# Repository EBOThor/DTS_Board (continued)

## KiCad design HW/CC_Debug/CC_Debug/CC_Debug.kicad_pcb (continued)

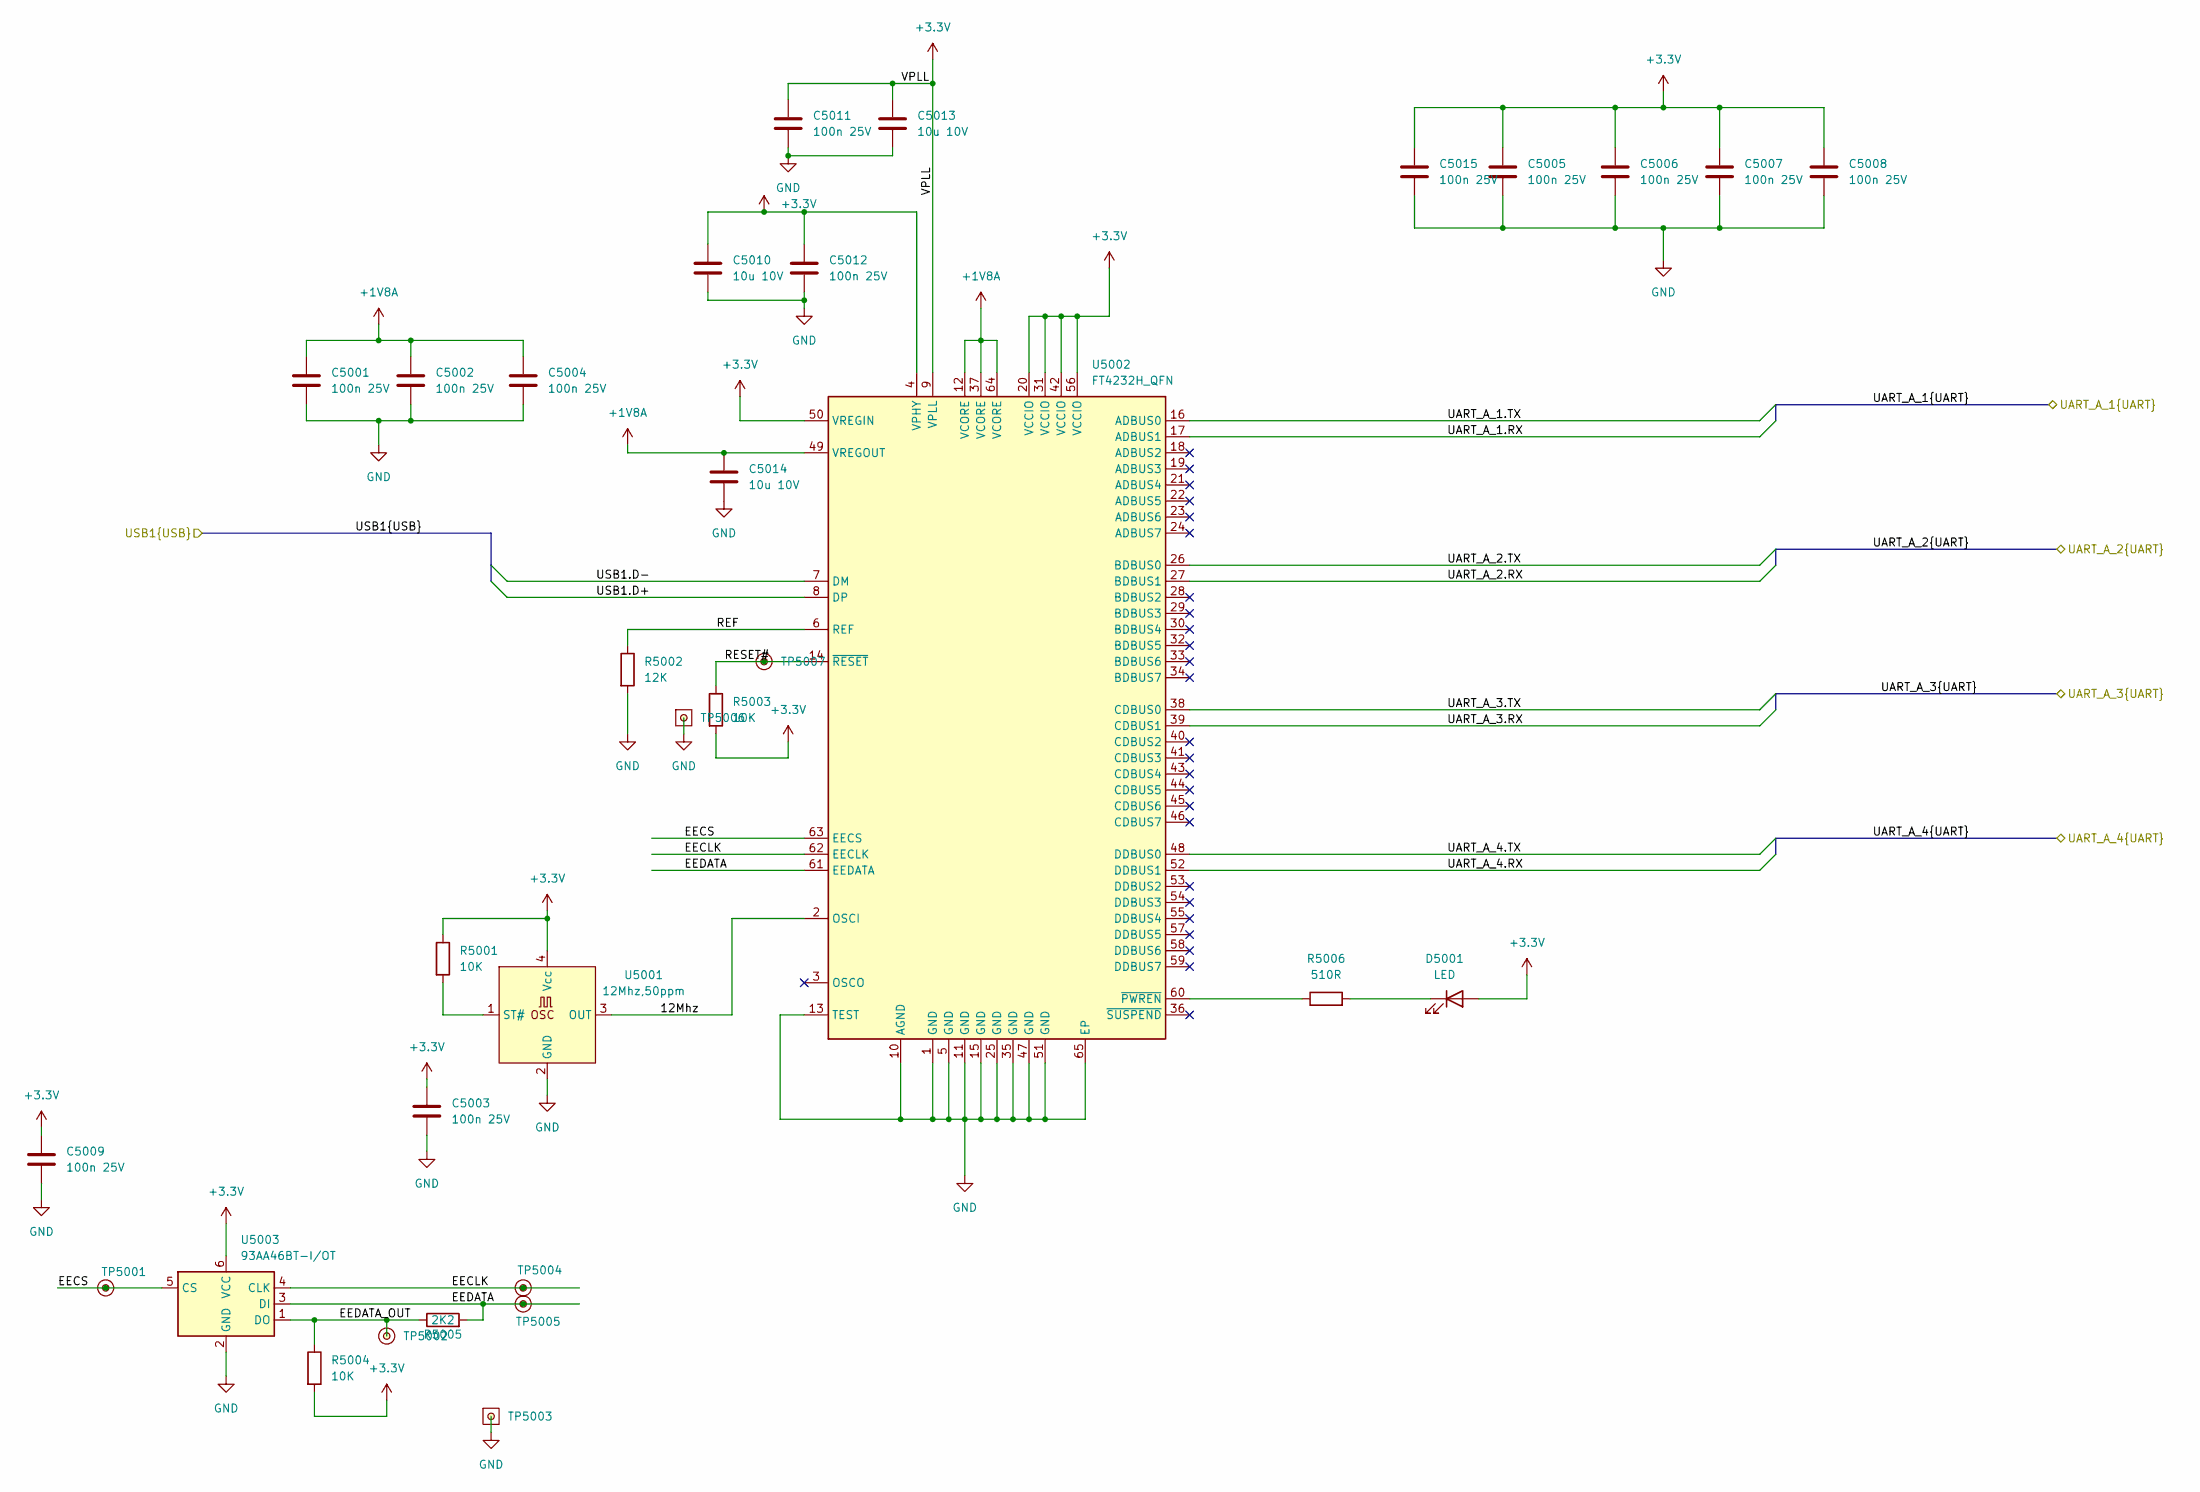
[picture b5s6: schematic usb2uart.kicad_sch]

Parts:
C5001, C5002, C5003, C5004, C5005, C5006, C5007, C5008, C5009, C5011, C5012, C5015: 100n 25V; C_0603_1608Metric; MPN C;C;T1;S;P0603;NA
C5010, C5013, C5014: 10u 10V; C_0603_1608Metric; MPN C;C;T1;S;P0603;NA
D5001: LED; LED_0603_1608Metric
R5001, R5003, R5004: 10K; R_0603_1608Metric; MPN R;G;T1;S;P0603;NA
R5002: 12K; R_0603_1608Metric; MPN R;G;T1;S;P0603;NA
R5005: 2K2; R_0603_1608Metric; MPN R;G;T1;S;P0603;NA
R5006: 510R; R_0603_1608Metric; MPN R;G;T1;S;P0603;NA
TP5001, TP5002, TP5004, TP5005, TP5007: TestPoint; TestPoint_THTPad_D1.0mm_Drill0.5mm
TP5003, TP5006: TestPoint; TestPoint_THTPad_1.0x1.0mm_Drill0.5mm
U5001: 12Mhz,50ppm; Oscillator_SMD_SeikoEpson_SG8002CE-4Pin_3.2x2.5mm; MPN SG3225CAN 12.0000M-TJGA6
U5002: FT4232H_QFN; QFN-64-1EP_9x9mm_P0.5mm_EP4.35x4.35mm; MPN FT4232HP
U5003: 93AA46BT-I/OT; SOT-23-6; MPN 93AA46BT-I/OT

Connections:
+1V8A: C5001.1, C5002.1, C5004.1, C5014.1, U5002.12 (VCORE), U5002.37 (VCORE), U5002.49 (VREGOUT), U5002.64 (VCORE)
+3.3V: C5003.1, C5005.1, C5006.1, C5007.1, C5008.1, C5009.1, C5010.1, C5011.1, C5012.1, C5013.1, C5015.1, D5001.2 (A), R5001.1, R5003.2, R5004.2, U5001.4 (Vcc), U5002.4 (VPHY), U5002.9 (VPLL), U5002.20 (VCCIO), U5002.31 (VCCIO), U5002.42 (VCCIO), U5002.50 (VREGIN), U5002.56 (VCCIO), U5003.6 (VCC); also elsewhere on the board
/Isolation_output/UART_A_1.RX: U5002.17 (ADBUS1); also elsewhere on the board
/Isolation_output/UART_A_1.TX: U5002.16 (ADBUS0); also elsewhere on the board
/Isolation_output/UART_A_2.RX: U5002.27 (BDBUS1); also elsewhere on the board
/Isolation_output/UART_A_2.TX: U5002.26 (BDBUS0); also elsewhere on the board
/Isolation_output/UART_A_3.RX: U5002.39 (CDBUS1); also elsewhere on the board
/Isolation_output/UART_A_3.TX: U5002.38 (CDBUS0); also elsewhere on the board
/Isolation_output/UART_A_4.RX: U5002.52 (DDBUS1); also elsewhere on the board
/Isolation_output/UART_A_4.TX: U5002.48 (DDBUS0); also elsewhere on the board
/USB1.D+: U5002.8 (DP); also elsewhere on the board
/USB1.D-: U5002.7 (DM); also elsewhere on the board
/USB2UART1/12Mhz: U5001.3 (OUT), U5002.2 (OSCI)
/USB2UART1/EECLK: TP5004.1, U5002.62 (EECLK), U5003.4 (CLK)
/USB2UART1/EECS: TP5001.1, U5002.63 (EECS), U5003.5 (CS)
/USB2UART1/EEDATA: R5005.2, TP5005.1, U5002.61 (EEDATA), U5003.3 (DI)
/USB2UART1/EEDATA_OUT: R5004.1, R5005.1, TP5002.1, U5003.1 (DO)
/USB2UART1/REF: R5002.1, U5002.6 (REF)
/USB2UART1/RESET#: R5003.1, TP5007.1, U5002.14 (~RESET)
GND: C5001.2, C5002.2, C5003.2, C5004.2, C5005.2, C5006.2, C5007.2, C5008.2, C5009.2, C5010.2, C5011.2, C5012.2, C5013.2, C5014.2, C5015.2, R5002.2, TP5003.1, TP5006.1, U5001.2 (GND), U5002.1 (GND), U5002.5 (GND), U5002.10 (AGND), U5002.11 (GND), U5002.13 (TEST), U5002.15 (GND), U5002.25 (GND), U5002.35 (GND), U5002.47 (GND), U5002.51 (GND), U5002.65 (EP), U5003.2 (GND); also elsewhere on the board
unnamed: D5001.1 (K), R5006.2
unnamed: R5001.2, U5001.1 (ST#)
unnamed: R5006.1, U5002.60 (~PWREN)

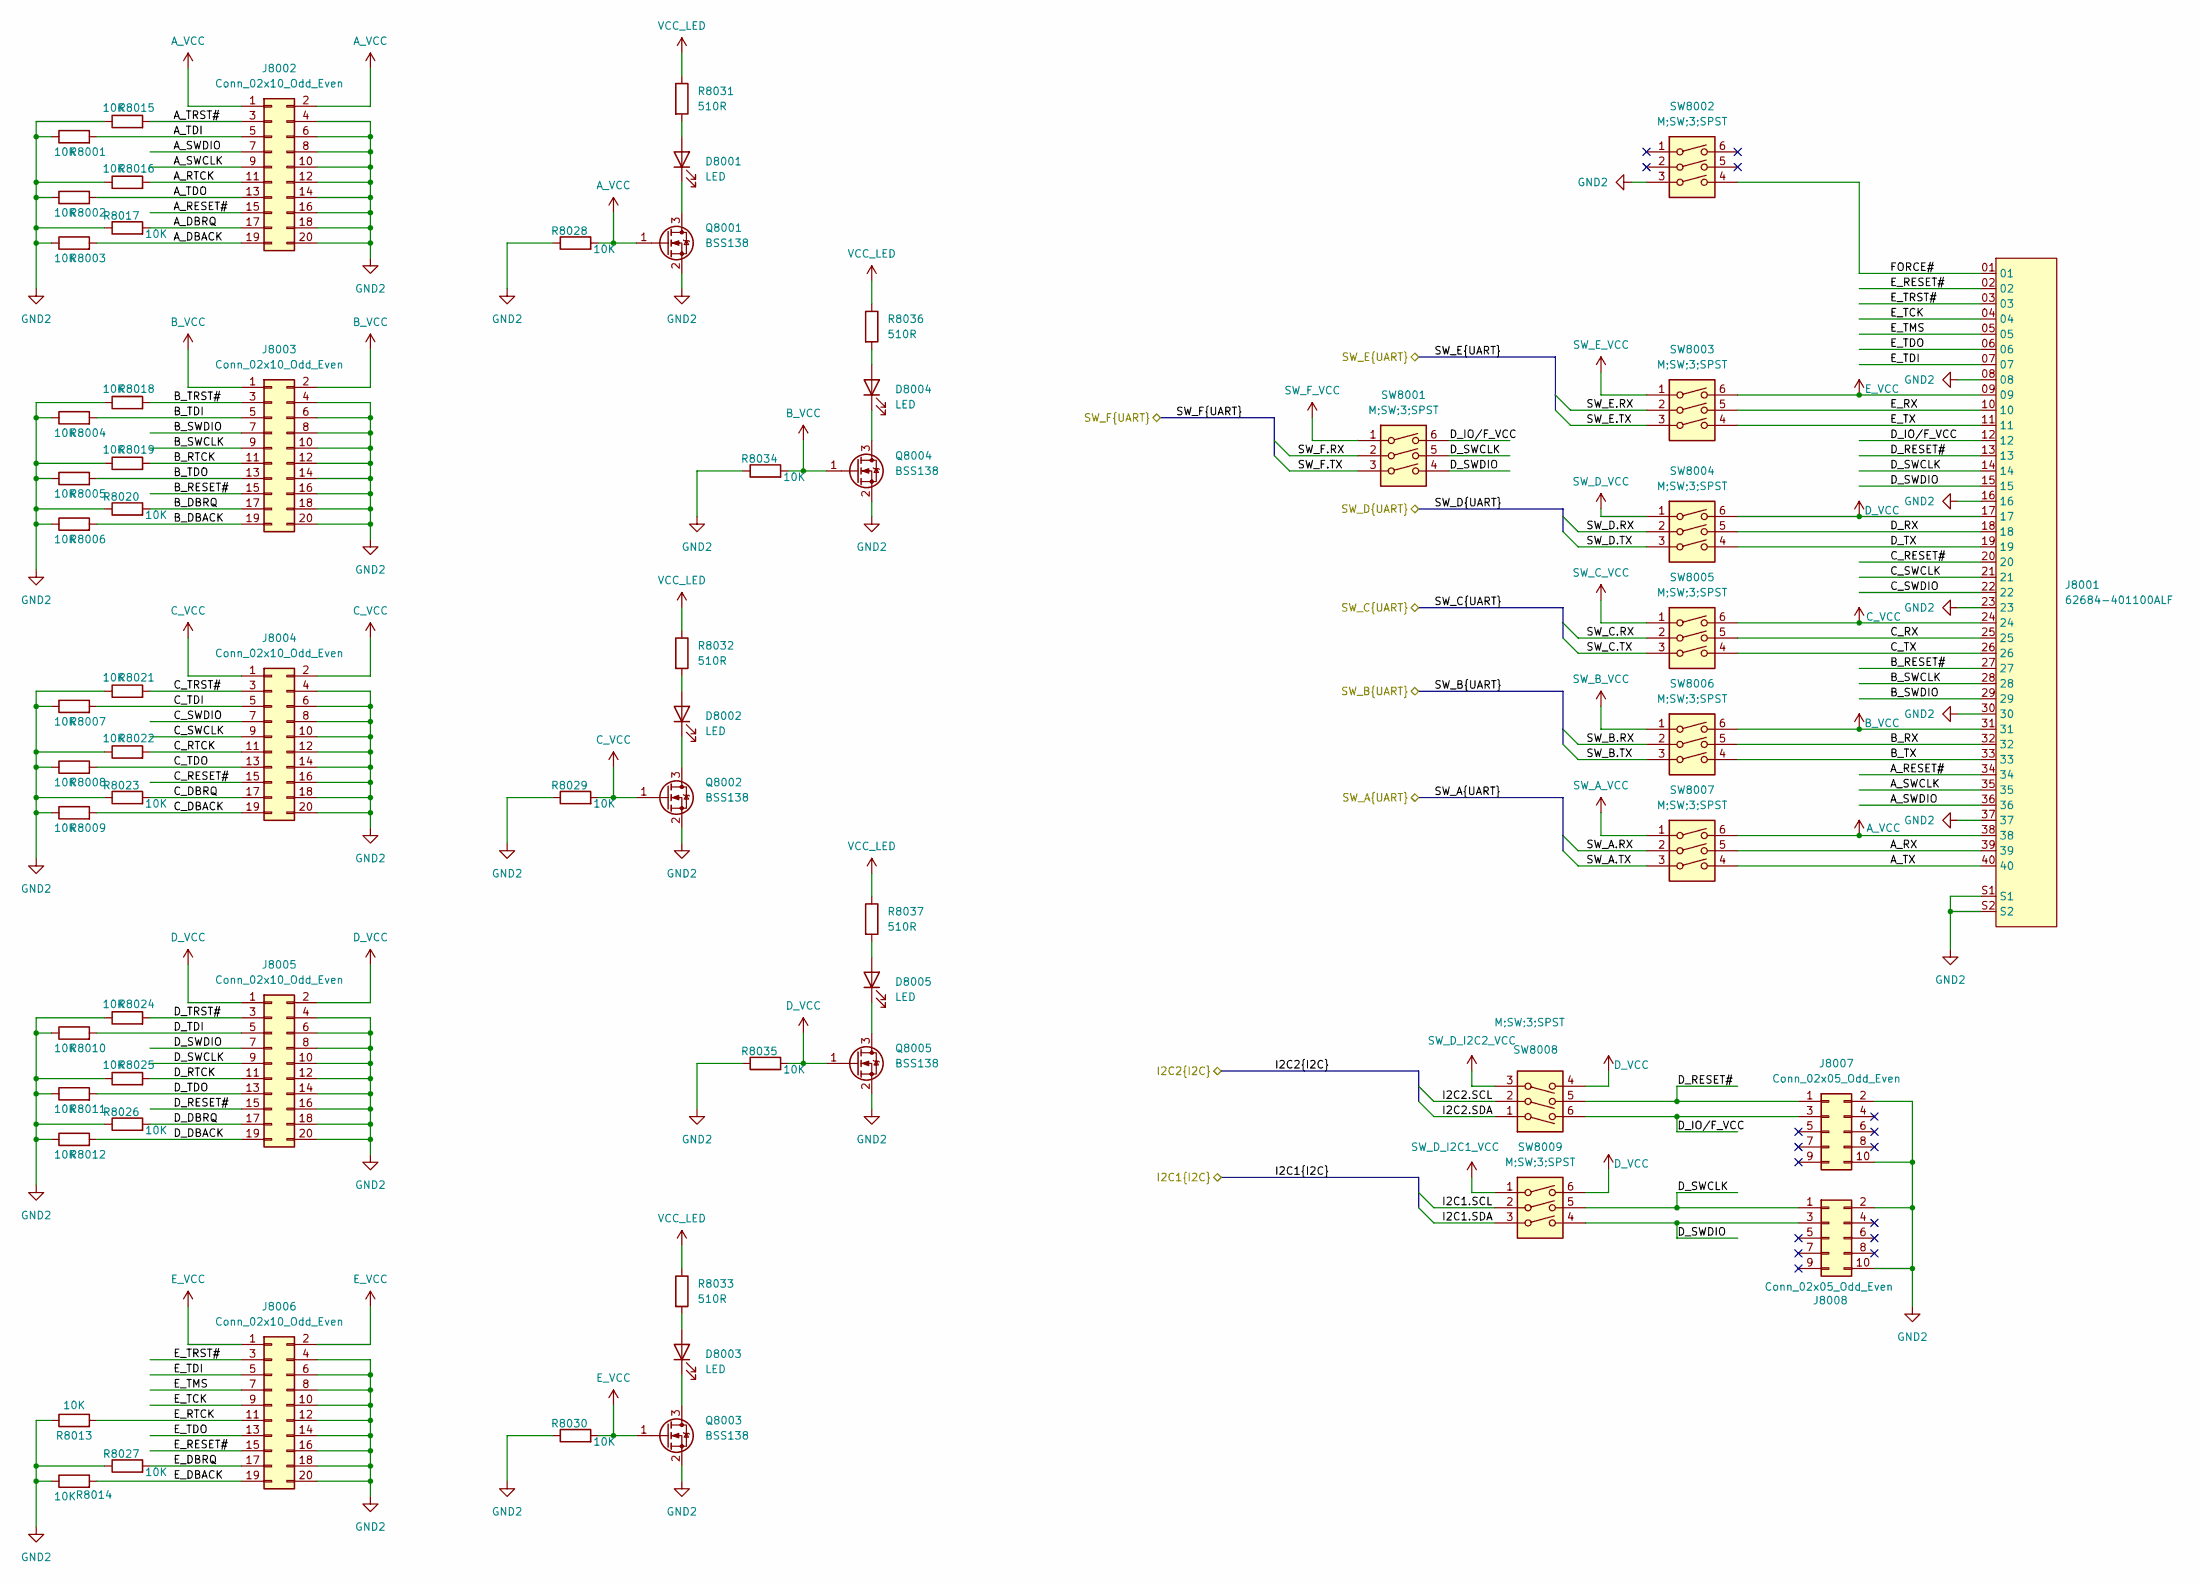
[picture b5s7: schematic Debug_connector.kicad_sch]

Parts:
D8001, D8002, D8003, D8004, D8005: LED; LED_0603_1608Metric
J8001: 62684-401100ALF; MPN 62684-401100ALF
J8002, J8003, J8004, J8005, J8006: Conn_02x10_Odd_Even; IDC-Header_2x10_P2.54mm_Vertical
J8007, J8008: Conn_02x05_Odd_Even; IDC-Header_2x05_P2.54mm_Vertical
Q8001, Q8002, Q8003, Q8004, Q8005: BSS138; SOT-23
R8001, R8002, R8003, R8004, R8005, R8006, R8007, R8008, R8009, R8010, R8011, R8012, R8013, R8014, R8015, R8016, R8017, R8018, R8019, R8020, R8021, R8022, R8023, R8024, R8025, R8026, R8027, R8028, R8029, R8030, R8034, R8035: 10K; R_0603_1608Metric; MPN R;G;T1;S;P0603;NA
R8031, R8032, R8033, R8036, R8037: 510R; R_0603_1608Metric; MPN R;G;T1;S;P0603;NA
SW8001, SW8002, SW8003, SW8004, SW8005, SW8006, SW8007, SW8008, SW8009: M;SW;3;SPST; SW_DS04-254-2-03BK-SMT; MPN DS04-254-2-03BK-SMT

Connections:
/Isolation_output/Debug_connector/A_DBACK: J8002.19, R8003.2
/Isolation_output/Debug_connector/A_DBRQ: J8002.17, R8017.2
/Isolation_output/Debug_connector/A_RESET#: J8001.34, J8002.15
/Isolation_output/Debug_connector/A_RTCK: J8002.11, R8016.2
/Isolation_output/Debug_connector/A_RX: J8001.39, SW8007.5
/Isolation_output/Debug_connector/A_SWCLK: J8001.35, J8002.9
/Isolation_output/Debug_connector/A_SWDIO: J8001.36, J8002.7
/Isolation_output/Debug_connector/A_TDI: J8002.5, R8001.2
/Isolation_output/Debug_connector/A_TDO: J8002.13, R8002.2
/Isolation_output/Debug_connector/A_TRST#: J8002.3, R8015.2
/Isolation_output/Debug_connector/A_TX: J8001.40, SW8007.4
/Isolation_output/Debug_connector/B_DBACK: J8003.19, R8006.2
/Isolation_output/Debug_connector/B_DBRQ: J8003.17, R8020.2
/Isolation_output/Debug_connector/B_RESET#: J8001.27, J8003.15
/Isolation_output/Debug_connector/B_RTCK: J8003.11, R8019.2
/Isolation_output/Debug_connector/B_RX: J8001.32, SW8006.5
/Isolation_output/Debug_connector/B_SWCLK: J8001.28, J8003.9
/Isolation_output/Debug_connector/B_SWDIO: J8001.29, J8003.7
/Isolation_output/Debug_connector/B_TDI: J8003.5, R8004.2
/Isolation_output/Debug_connector/B_TDO: J8003.13, R8005.2
/Isolation_output/Debug_connector/B_TRST#: J8003.3, R8018.2
/Isolation_output/Debug_connector/B_TX: J8001.33, SW8006.4
/Isolation_output/Debug_connector/C_DBACK: J8004.19, R8009.2
/Isolation_output/Debug_connector/C_DBRQ: J8004.17, R8023.2
/Isolation_output/Debug_connector/C_RESET#: J8001.20, J8004.15
/Isolation_output/Debug_connector/C_RTCK: J8004.11, R8022.2
/Isolation_output/Debug_connector/C_RX: J8001.25, SW8005.5
/Isolation_output/Debug_connector/C_SWCLK: J8001.21, J8004.9
/Isolation_output/Debug_connector/C_SWDIO: J8001.22, J8004.7
/Isolation_output/Debug_connector/C_TDI: J8004.5, R8007.2
/Isolation_output/Debug_connector/C_TDO: J8004.13, R8008.2
/Isolation_output/Debug_connector/C_TRST#: J8004.3, R8021.2
/Isolation_output/Debug_connector/C_TX: J8001.26, SW8005.4
/Isolation_output/Debug_connector/D_DBACK: J8005.19, R8012.2
/Isolation_output/Debug_connector/D_DBRQ: J8005.17, R8026.2
/Isolation_output/Debug_connector/D_IO/F_VCC: J8001.12, J8007.3, SW8001.6, SW8008.6
/Isolation_output/Debug_connector/D_RESET#: J8001.13, J8005.15, J8007.1, SW8008.5
/Isolation_output/Debug_connector/D_RTCK: J8005.11, R8025.2
/Isolation_output/Debug_connector/D_RX: J8001.18, SW8004.5
/Isolation_output/Debug_connector/D_SWCLK: J8001.14, J8005.9, J8008.1, SW8001.5, SW8009.5
/Isolation_output/Debug_connector/D_SWDIO: J8001.15, J8005.7, J8008.3, SW8001.4, SW8009.4
/Isolation_output/Debug_connector/D_TDI: J8005.5, R8010.2
/Isolation_output/Debug_connector/D_TDO: J8005.13, R8011.2
/Isolation_output/Debug_connector/D_TRST#: J8005.3, R8024.2
/Isolation_output/Debug_connector/D_TX: J8001.19, SW8004.4
/Isolation_output/Debug_connector/E_DBACK: J8006.19, R8014.2
/Isolation_output/Debug_connector/E_DBRQ: J8006.17, R8027.2
/Isolation_output/Debug_connector/E_RESET#: J8001.02, J8006.15
/Isolation_output/Debug_connector/E_RTCK: J8006.11, R8013.2
/Isolation_output/Debug_connector/E_RX: J8001.10, SW8003.5
/Isolation_output/Debug_connector/E_TCK: J8001.04, J8006.9
/Isolation_output/Debug_connector/E_TDI: J8001.07, J8006.5
/Isolation_output/Debug_connector/E_TDO: J8001.06, J8006.13
/Isolation_output/Debug_connector/E_TMS: J8001.05, J8006.7
/Isolation_output/Debug_connector/E_TRST#: J8001.03, J8006.3
/Isolation_output/Debug_connector/E_TX: J8001.11, SW8003.4
/Isolation_output/Debug_connector/FORCE#: J8001.01, SW8002.4
/Isolation_output/I2C1.SCL: SW8009.2; also elsewhere on the board
/Isolation_output/I2C1.SDA: SW8009.3; also elsewhere on the board
/Isolation_output/I2C2.SCL: SW8008.2; also elsewhere on the board
/Isolation_output/I2C2.SDA: SW8008.1; also elsewhere on the board
/Isolation_output/SW_A.RX: SW8007.2; also elsewhere on the board
/Isolation_output/SW_A.TX: SW8007.3; also elsewhere on the board
/Isolation_output/SW_B.RX: SW8006.2; also elsewhere on the board
/Isolation_output/SW_B.TX: SW8006.3; also elsewhere on the board
/Isolation_output/SW_C.RX: SW8005.2; also elsewhere on the board
/Isolation_output/SW_C.TX: SW8005.3; also elsewhere on the board
/Isolation_output/SW_D.RX: SW8004.2; also elsewhere on the board
/Isolation_output/SW_D.TX: SW8004.3; also elsewhere on the board
/Isolation_output/SW_E.RX: SW8003.2; also elsewhere on the board
/Isolation_output/SW_E.TX: SW8003.3; also elsewhere on the board
/Isolation_output/SW_F.RX: SW8001.2; also elsewhere on the board
/Isolation_output/SW_F.TX: SW8001.3; also elsewhere on the board
A_VCC: J8001.38, J8002.1, J8002.2, Q8001.1 (G), R8028.2, SW8007.6
B_VCC: J8001.31, J8003.1, J8003.2, Q8004.1 (G), R8034.2, SW8006.6
C_VCC: J8001.24, J8004.1, J8004.2, Q8002.1 (G), R8029.2, SW8005.6
D_VCC: J8001.17, J8005.1, J8005.2, Q8005.1 (G), R8035.2, SW8004.6, SW8008.4, SW8009.6
E_VCC: J8001.09, J8006.1, J8006.2, Q8003.1 (G), R8030.2, SW8003.6
GND2: J8001.08, J8001.16, J8001.23, J8001.30, J8001.37, J8001.S1, J8001.S2, J8002.4, J8002.6, J8002.8, J8002.10, J8002.12, J8002.14, J8002.16, J8002.18, J8002.20, J8003.4, J8003.6, J8003.8, J8003.10, J8003.12, J8003.14, J8003.16, J8003.18, J8003.20, J8004.4, J8004.6, J8004.8, J8004.10, J8004.12, J8004.14, J8004.16, J8004.18, J8004.20, J8005.4, J8005.6, J8005.8, J8005.10, J8005.12, J8005.14, J8005.16, J8005.18, J8005.20, J8006.4, J8006.6, J8006.8, J8006.10, J8006.12, J8006.14, J8006.16, J8006.18, J8006.20, J8007.2, J8007.10, J8008.2, J8008.10, Q8001.2 (S), Q8002.2 (S), Q8003.2 (S), Q8004.2 (S), Q8005.2 (S), R8001.1, R8002.1, R8003.1, R8004.1, R8005.1, R8006.1, R8007.1, R8008.1, R8009.1, R8010.1, R8011.1, R8012.1, R8013.1, R8014.1, R8015.1, R8016.1, R8017.1, R8018.1, R8019.1, R8020.1, R8021.1, R8022.1, R8023.1, R8024.1, R8025.1, R8026.1, R8027.1, R8028.1, R8029.1, R8030.1, R8034.1, R8035.1, SW8002.3; also elsewhere on the board
unnamed: D8001.2 (A), R8031.2
unnamed: D8001.1 (K), Q8001.3 (D)
unnamed: D8002.2 (A), R8032.2
unnamed: D8002.1 (K), Q8002.3 (D)
unnamed: D8003.2 (A), R8033.2
unnamed: D8003.1 (K), Q8003.3 (D)
unnamed: D8004.2 (A), R8036.2
unnamed: D8004.1 (K), Q8004.3 (D)
unnamed: D8005.2 (A), R8037.2
unnamed: D8005.1 (K), Q8005.3 (D)
SW_A_VCC: SW8007.1; also elsewhere on the board
SW_B_VCC: SW8006.1; also elsewhere on the board
SW_C_VCC: SW8005.1; also elsewhere on the board
SW_D_I2C1_VCC: SW8009.1; also elsewhere on the board
SW_D_I2C2_VCC: SW8008.3; also elsewhere on the board
SW_D_VCC: SW8004.1; also elsewhere on the board
SW_E_VCC: SW8003.1; also elsewhere on the board
SW_F_VCC: SW8001.1; also elsewhere on the board
VCC_LED: R8031.1, R8032.1, R8033.1, R8036.1, R8037.1; also elsewhere on the board

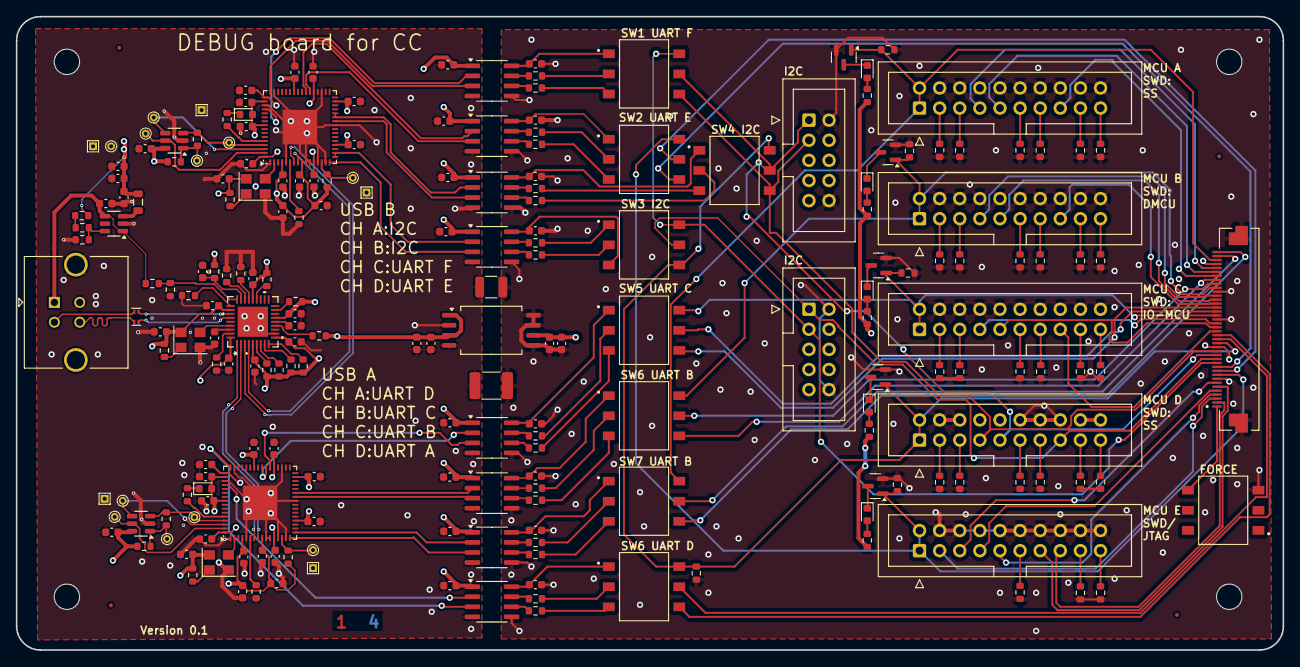
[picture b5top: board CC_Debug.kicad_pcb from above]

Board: 4 copper layers, 160.0 x 80.0 mm, 223 parts (0 on the bottom side), 183 nets.

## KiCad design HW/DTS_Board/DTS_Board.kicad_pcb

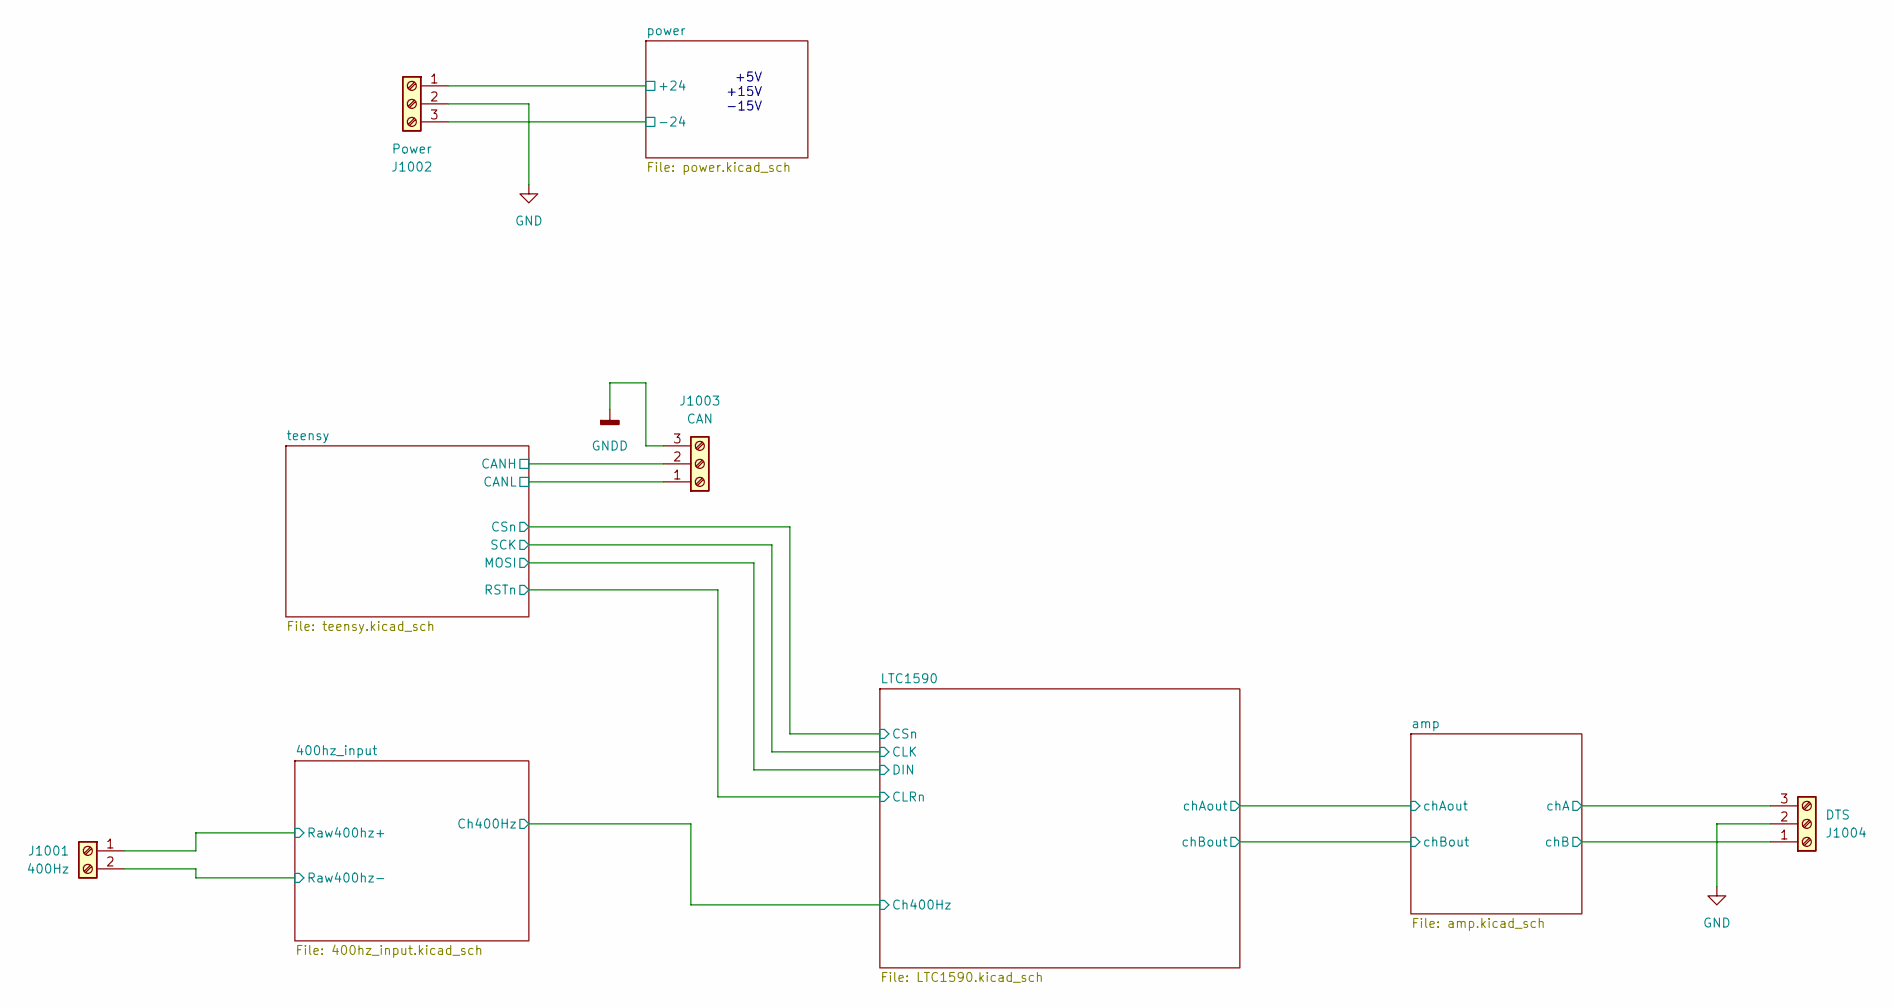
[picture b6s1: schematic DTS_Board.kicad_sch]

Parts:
J1001: 400Hz; PhoenixContact_MCV_1,5_2-G-5.08_1x02_P5.08mm_Vertical
J1002: Power; PhoenixContact_MCV_1,5_3-G-5.08_1x03_P5.08mm_Vertical
J1003: CAN; PhoenixContact_MCV_1,5_3-G-5.08_1x03_P5.08mm_Vertical
J1004: DTS; PhoenixContact_MCV_1,5_3-G-5.08_1x03_P5.08mm_Vertical

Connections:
/400hz_input/Raw400hz+: J1001.1; also elsewhere on the board
/400hz_input/Raw400hz-: J1001.2; also elsewhere on the board
/amp/chA: J1004.3; also elsewhere on the board
/amp/chB: J1004.1; also elsewhere on the board
/power/+24: J1002.1; also elsewhere on the board
/power/-24: J1002.3; also elsewhere on the board
/teensy/CANH: J1003.2; also elsewhere on the board
/teensy/CANL: J1003.1; also elsewhere on the board
GND: J1002.2, J1004.2; also elsewhere on the board
GNDD: J1003.3; also elsewhere on the board

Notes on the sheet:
+5V +15V -15V

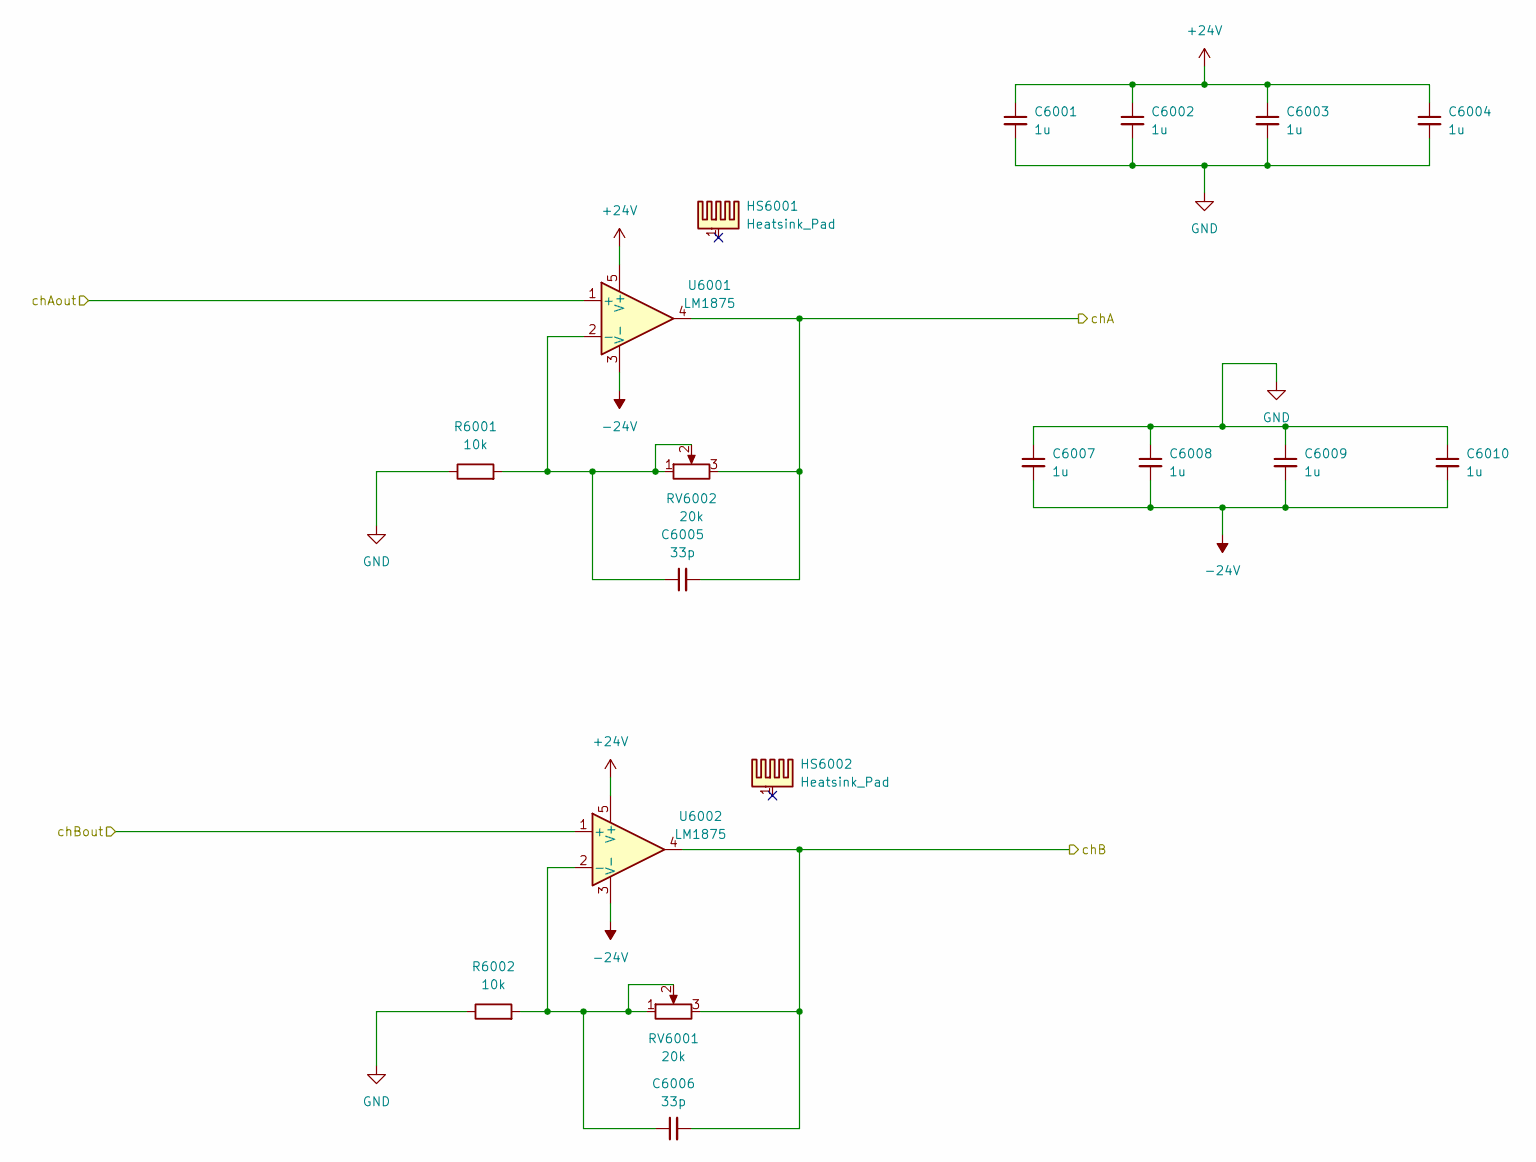
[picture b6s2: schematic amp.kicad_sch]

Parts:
C6001, C6002, C6003, C6004, C6007, C6008, C6009, C6010: 1u; C_1206_3216Metric
C6005, C6006: 33p; C_0805_2012Metric
HS6001, HS6002: Heatsink_Pad; Heatsink_Fischer_SK104-STCB_35x13mm__2xDrill3.5mm_ScrewM3
R6001, R6002: 10k; R_0805_2012Metric
RV6001, RV6002: 20k; Potentiometer_Bourns_3266W_Vertical
U6001, U6002: LM1875; TO-220-5_P3.4x3.7mm_StaggerOdd_Lead3.8mm_Vertical

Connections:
+24V: C6001.1, C6002.1, C6003.1, C6004.1, U6001.5 (V+), U6002.5 (V+); also elsewhere on the board
-24V: C6007.2, C6008.2, C6009.2, C6010.2, U6001.3 (V-), U6002.3 (V-); also elsewhere on the board
/LTC1590/chAout: U6001.1 (+); also elsewhere on the board
/LTC1590/chBout: U6002.1 (+); also elsewhere on the board
/amp/chA: C6005.2, RV6002.3, U6001.4; also elsewhere on the board
/amp/chB: C6006.2, RV6001.3, U6002.4; also elsewhere on the board
GND: C6001.2, C6002.2, C6003.2, C6004.2, C6007.1, C6008.1, C6009.1, C6010.1, R6001.1, R6002.1; also elsewhere on the board
unnamed: C6005.1, R6001.2, RV6002.1, RV6002.2, U6001.2 (-)
unnamed: C6006.1, R6002.2, RV6001.1, RV6001.2, U6002.2 (-)

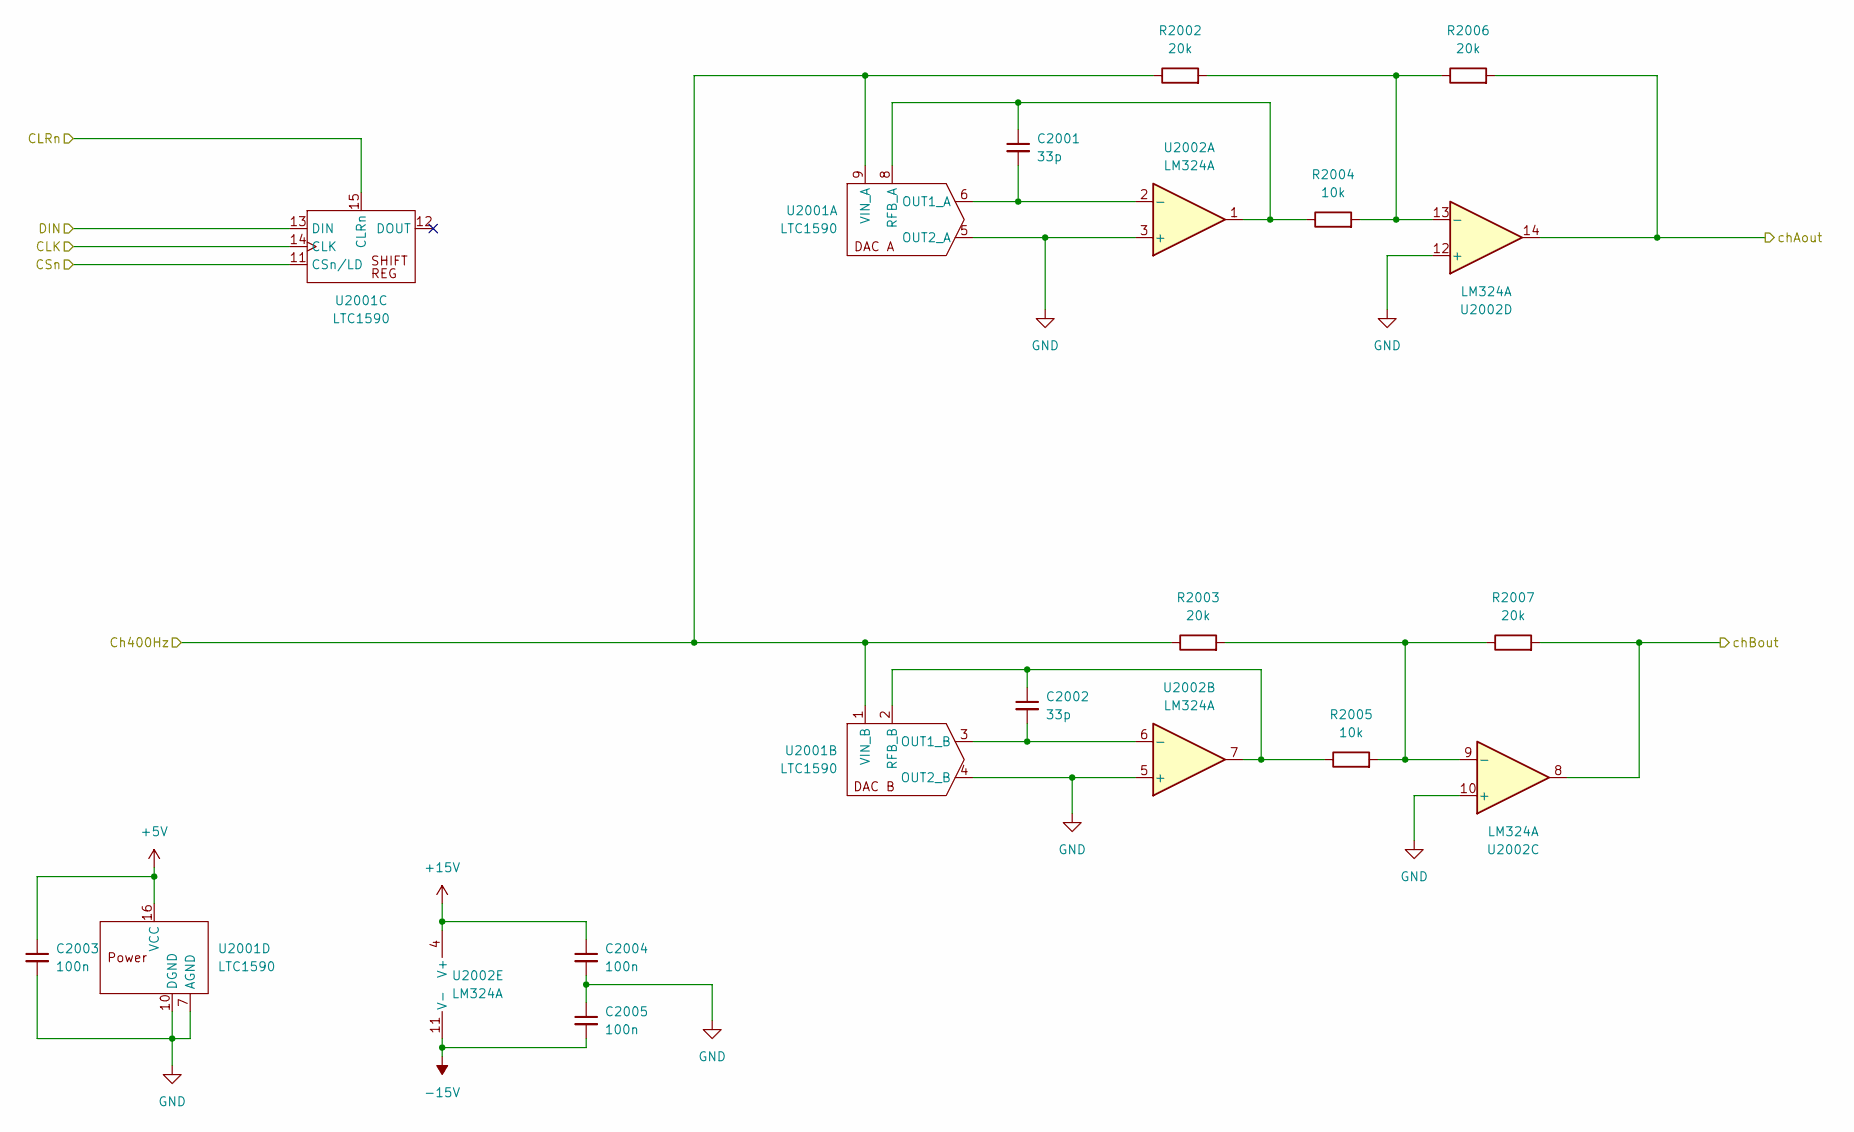
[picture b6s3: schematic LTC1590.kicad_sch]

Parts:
C2001, C2002: 33p; C_0805_2012Metric
C2003, C2004, C2005: 100n; C_0805_2012Metric
R2002, R2003, R2006, R2007: 20k; R_0805_2012Metric
R2004, R2005: 10k; R_0805_2012Metric
U2001: LTC1590; DIP-16_W7.62mm
U2002: LM324A; DIP-14_W7.62mm

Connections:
+5V: C2003.1, U2001.16 (VCC); also elsewhere on the board
+15V: C2004.1, U2002.4 (V+); also elsewhere on the board
-15V: C2005.2, U2002.11 (V-); also elsewhere on the board
/400hz_input/Ch400Hz: R2002.1, R2003.1, U2001.1 (VIN_B), U2001.9 (VIN_A); also elsewhere on the board
/LTC1590/CLK: U2001.14 (CLK); also elsewhere on the board
/LTC1590/CLRn: U2001.15 (CLRn); also elsewhere on the board
/LTC1590/CSn: U2001.11 (CSn/LD); also elsewhere on the board
/LTC1590/DIN: U2001.13 (DIN); also elsewhere on the board
/LTC1590/chAout: R2006.2, U2002.14; also elsewhere on the board
/LTC1590/chBout: R2007.2, U2002.8; also elsewhere on the board
GND: C2003.2, C2004.2, C2005.1, U2001.4 (OUT2_B), U2001.5 (OUT2_A), U2001.7 (AGND), U2001.10 (DGND), U2002.3 (+), U2002.5 (+), U2002.10 (+), U2002.12 (+); also elsewhere on the board
unnamed: C2001.2, U2001.6 (OUT1_A), U2002.2 (-)
unnamed: C2001.1, R2004.1, U2001.8 (RFB_A), U2002.1
unnamed: C2002.2, U2001.3 (OUT1_B), U2002.6 (-)
unnamed: C2002.1, R2005.1, U2001.2 (RFB_B), U2002.7
unnamed: R2003.2, R2005.2, R2007.1, U2002.9 (-)
unnamed: R2002.2, R2004.2, R2006.1, U2002.13 (-)

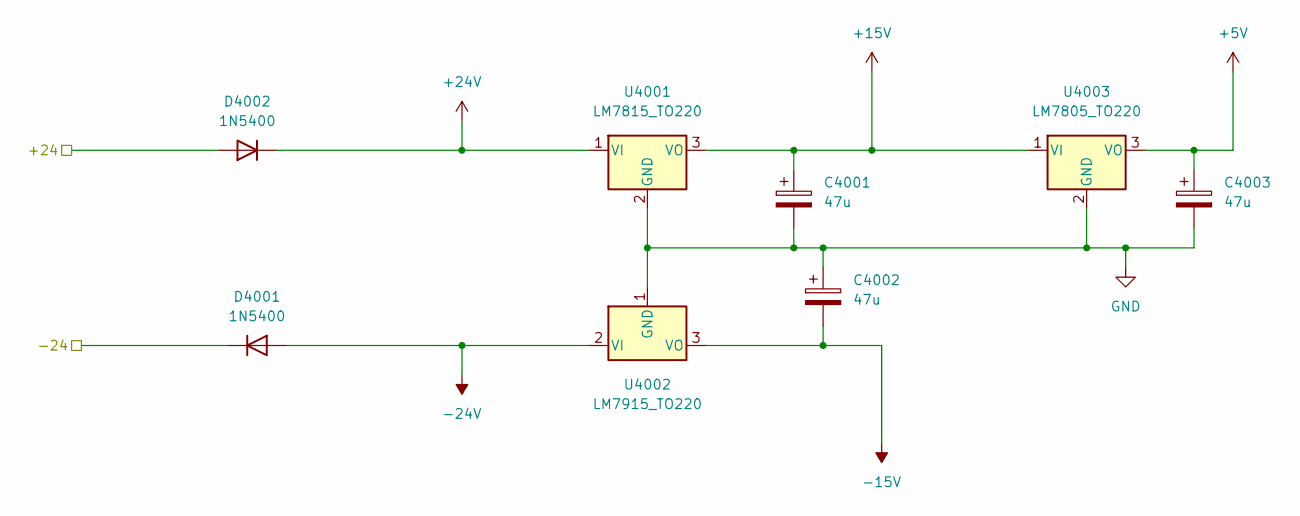
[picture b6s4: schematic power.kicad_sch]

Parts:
C4001, C4002, C4003: 47u; CP_Radial_D8.0mm_P3.80mm
D4001, D4002: 1N5400; D_DO-201AD_P15.24mm_Horizontal
U4001: LM7815_TO220; TO-220-3_Vertical
U4002: LM7915_TO220; TO-220-3_Vertical
U4003: LM7805_TO220; TO-220-3_Vertical

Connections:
+5V: C4003.1, U4003.3 (VO); also elsewhere on the board
+15V: C4001.1, U4001.3 (VO), U4003.1 (VI); also elsewhere on the board
+24V: D4002.1 (K), U4001.1 (VI); also elsewhere on the board
-15V: C4002.2, U4002.3 (VO); also elsewhere on the board
-24V: D4001.2 (A), U4002.2 (VI); also elsewhere on the board
/power/+24: D4002.2 (A); also elsewhere on the board
/power/-24: D4001.1 (K); also elsewhere on the board
GND: C4001.2, C4002.1, C4003.2, U4001.2 (GND), U4002.1 (GND), U4003.2 (GND); also elsewhere on the board
